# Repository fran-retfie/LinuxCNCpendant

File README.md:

# LinuxCNC Pendant

This is a pendant for linuxCNC using an SparkFun SAMD21 Dev Breakout but with little or no changes to the program you can run this on other arduino UNO style board.

## Getting Started

**warning** this project may require some changes to make it work properly with your hardware

The project is divided in 4 directories:
* model - a FreeCAD project of the enclosure and a G-code for cutting it
* PCB - a kicad project of the PCB
* Arduino
* Python

### Prerequisites

I suggest you check the PCB before starting beacause there will be maybe some issues: (eg: spacings, SMD parts filipped, ecc..)

for running python program you need the following packages:
* linuxCNC
* TkInter
* tk-tools
* pyserial

### Installing

Upload arduino 'remoteCNC' project on the board and run the python 'remoteCNC' program on a PC with linuxCNC running

## Running the tests

To check pushbuttons and analog input use the 'remoteCNC_test' program on both arduino and PC side.

## Contributing

This project expecially the software in not completed so you are free to contribuite in any way you want.

## Authors

* **Francesco Osti** - *Initial work* - [fran-retfie](https://github.com/fran-retfie)

See also the list of [contributors](https://github.com/fran-retfie/LinuxCNCpendant/contributors)

## License

This project is licensed under the MIT License - see the [LICENSE.md](LICENSE.md) file for details

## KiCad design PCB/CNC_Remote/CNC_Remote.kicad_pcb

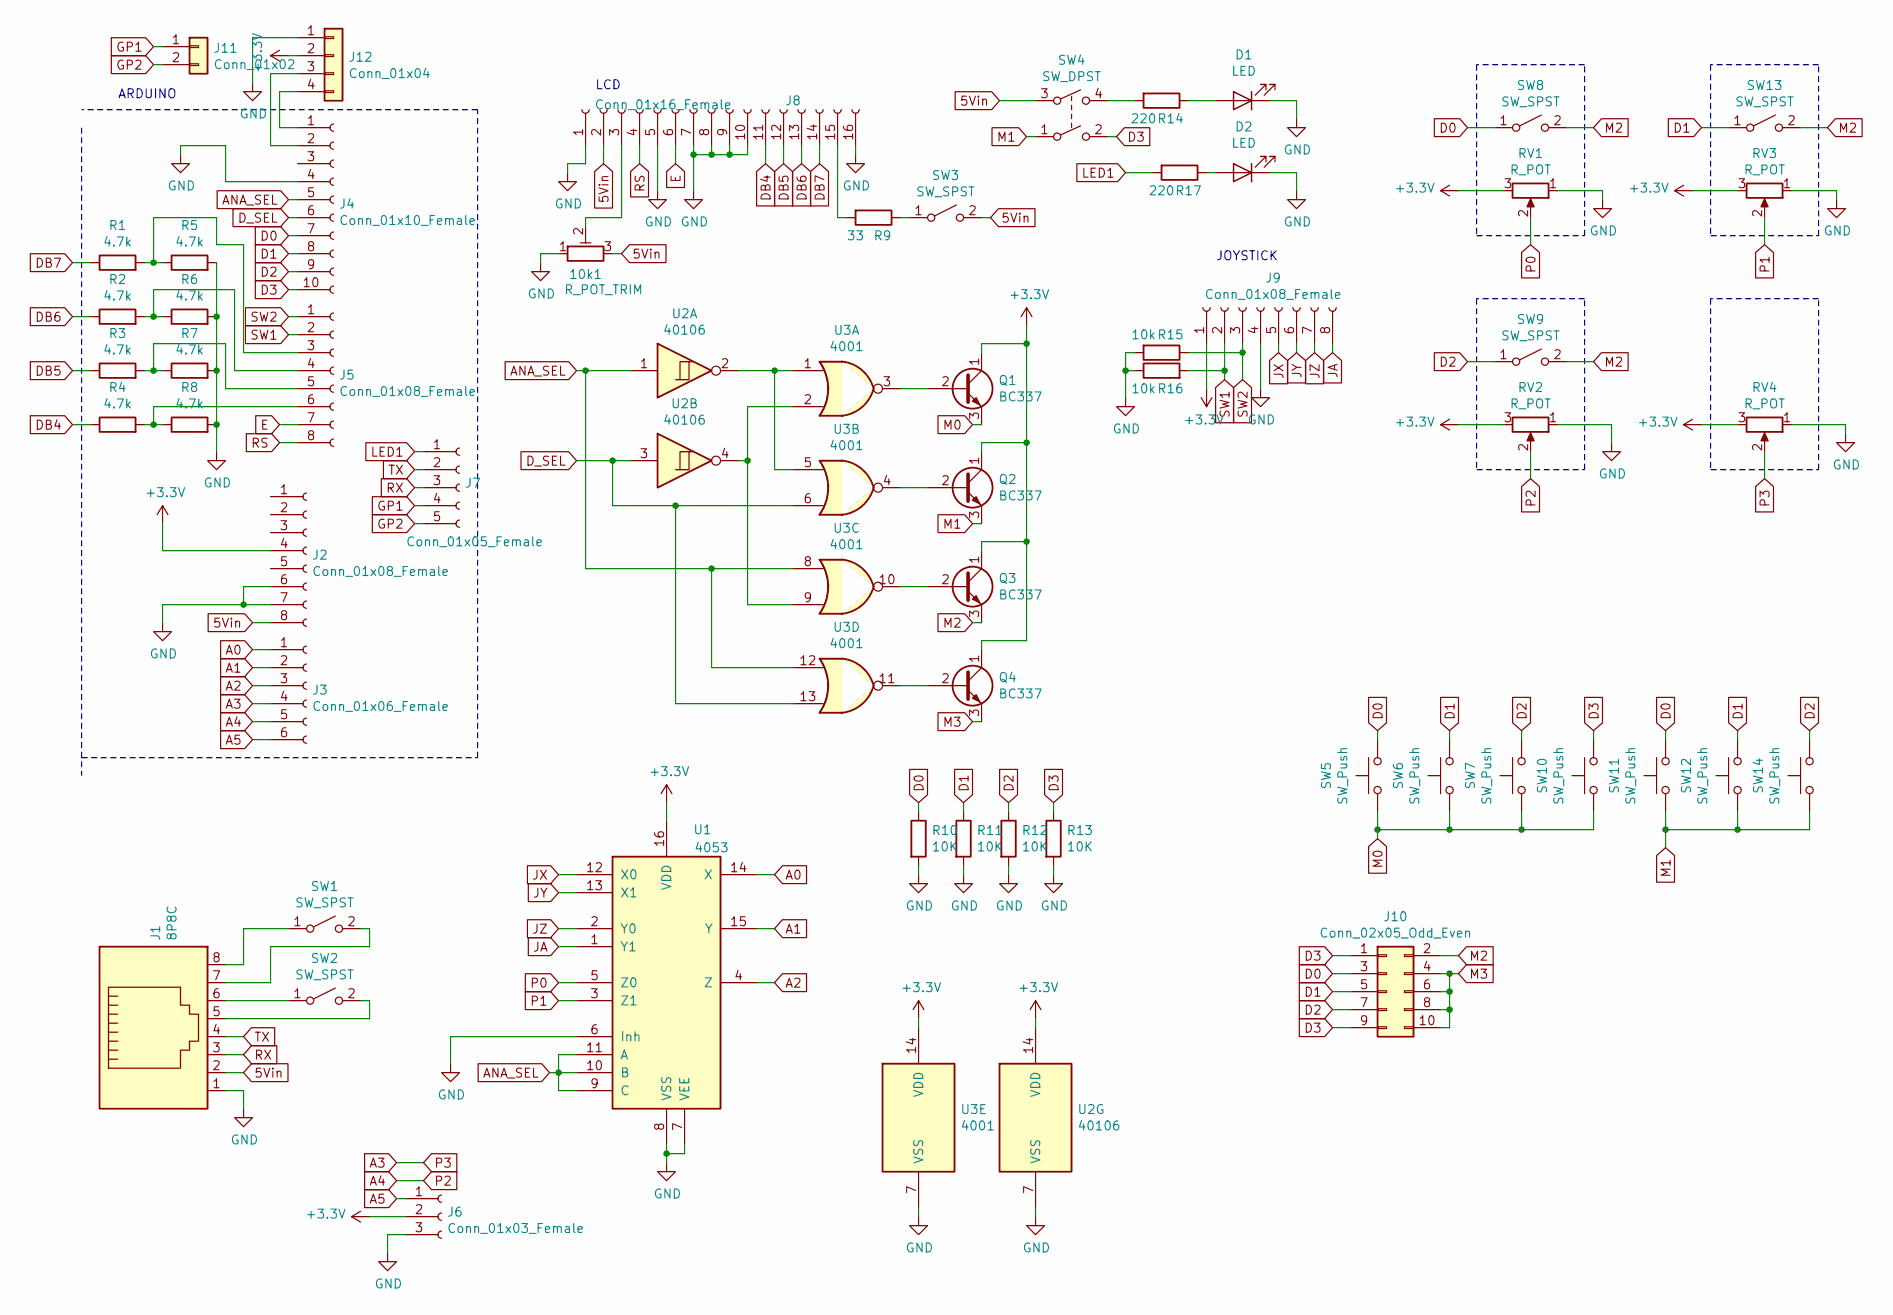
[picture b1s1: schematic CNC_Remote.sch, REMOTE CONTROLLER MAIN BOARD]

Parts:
10k1: R_POT_TRIM; Potentiometer_Piher_PT-10-V10_Vertical
D1, D2: LED; PinHeader_1x02_P2.54mm_Vertical
J1: 8P8C; RJ45_Amphenol_54602-x08_Horizontal
J2, J5, J9: Conn_01x08_Female; PinHeader_1x08_P2.54mm_Vertical
J3: Conn_01x06_Female; PinHeader_1x06_P2.54mm_Vertical
J4: Conn_01x10_Female; PinHeader_1x10_P2.54mm_Vertical
J6: Conn_01x03_Female; PinHeader_1x03_P2.54mm_Vertical
J7: Conn_01x05_Female; PinHeader_1x05_P2.54mm_Vertical
J8: Conn_01x16_Female; PinHeader_1x16_P2.54mm_Vertical
J10: Conn_02x05_Odd_Even; PinHeader_2x05_P2.54mm_Horizontal
J11: Conn_01x02; PinHeader_1x02_P2.54mm_Vertical
J12: Conn_01x04; PinHeader_1x04_P2.54mm_Vertical
Q1, Q2, Q3, Q4: BC337; TO-92_Inline
R1, R2, R3, R4, R5, R6, R7, R8: 4.7k; R_Axial_DIN0207_L6.3mm_D2.5mm_P10.16mm_Horizontal
R9: 33; R_Axial_DIN0207_L6.3mm_D2.5mm_P10.16mm_Horizontal
R10, R11, R12, R13: 10K; R_Axial_DIN0207_L6.3mm_D2.5mm_P10.16mm_Horizontal
R14, R17: 220; R_Axial_DIN0207_L6.3mm_D2.5mm_P10.16mm_Horizontal
R15, R16: 10k; R_Axial_DIN0207_L6.3mm_D2.5mm_P10.16mm_Horizontal
RV1, RV2, RV3, RV4: R_POT; PinHeader_1x03_P2.54mm_Vertical
SW1, SW2, SW3, SW8, SW9, SW13: SW_SPST; PinHeader_1x02_P2.54mm_Vertical
SW4: SW_DPST; PinHeader_1x04_P2.54mm_Vertical
SW5, SW6, SW7, SW10, SW11, SW12, SW14: SW_Push; PinHeader_1x02_P2.54mm_Vertical
U1: 4053; SOIC-16W_5.3x10.2mm_P1.27mm
U2: 40106; DIP-14_W7.62mm_Socket_LongPads
U3: 4001; DIP-14_W7.62mm_Socket_LongPads

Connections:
5Vin: 10k1.3, J1.2, J2.8, J8.2, SW3.2 (B), SW4.3
+3V3: J2.4, J6.2, J9.1, J12.2, Q1.1 (C), Q2.1 (C), Q3.1 (C), Q4.1 (C), RV1.3, RV2.3, RV3.3, RV4.3, U1.16 (VDD), U2.14 (VDD), U3.14 (VDD)
A0: J3.1, U1.14 (X)
A1: J3.2, U1.15 (Y)
A2: J3.3, U1.4 (Z)
A3: J3.4, RV4.2
A4: J3.5, RV2.2
A5: J3.6, J6.1
ANA_SEL: J4.5, U1.9 (C), U1.10 (B), U1.11 (A), U2.1, U3.8, U3.12
D0: J4.7, J10.3, R10.1, SW5.2, SW8.1 (A), SW11.2
D1: J4.8, J10.5, R11.1, SW6.2, SW12.2, SW13.1 (A)
D2: J4.9, J10.7, R12.1, SW7.2, SW9.1 (A), SW14.2
D3: J4.10, J10.1, J10.9, R13.1, SW4.2, SW10.2
DB4: J8.11, R4.1
DB5: J8.12, R3.1
DB6: J8.13, R2.1
DB7: J8.14, R1.1
D_SEL: J4.6, U2.3, U3.6, U3.13
E: J5.7, J8.6
GND: 10k1.1, D1.1 (K), D2.1 (K), J1.1, J2.6, J2.7, J4.4, J6.3, J8.1, J8.5, J8.7, J8.8, J8.9, J8.10, J8.16, J9.4, J12.1, R5.2, R6.2, R7.2, R8.2, R10.2, R11.2, R12.2, R13.2, R15.2, R16.1, RV1.1, RV2.1, RV3.1, RV4.1, U1.6 (Inh), U1.7 (VEE), U1.8 (VSS), U2.7 (VSS), U3.7 (VSS)
GP1: J7.4, J11.1
GP2: J7.5, J11.2
JA: J9.8, U1.1 (Y1)
JX: J9.5, U1.12 (X0)
JY: J9.6, U1.13 (X1)
JZ: J9.7, U1.2 (Y0)
LED1: J7.1, R17.2
M0: Q1.3 (E), SW5.1, SW6.1, SW7.1, SW10.1
M1: Q2.3 (E), SW4.1, SW11.1, SW12.1, SW14.1
M2: J10.2, Q3.3 (E), SW8.2 (B), SW9.2 (B), SW13.2 (B)
M3: J10.4, J10.6, J10.8, J10.10, Q4.3 (E)
unnamed: 10k1.2, J8.3
unnamed: D1.2 (A), R14.1
unnamed: D2.2 (A), R17.1
unnamed: J1.5, SW2.2 (B)
unnamed: J1.6, SW2.1 (A)
unnamed: J1.7, SW1.2 (B)
unnamed: J1.8, SW1.1 (A)
unnamed: J5.3, R1.2, R5.1
unnamed: J5.4, R2.2, R6.1
unnamed: J5.5, R3.2, R7.1
unnamed: J5.6, R4.2, R8.1
unnamed: J8.15, R9.2
unnamed: J4.2, J12.3
unnamed: J4.1, J12.4
unnamed: Q1.2 (B), U3.3
unnamed: Q2.2 (B), U3.4
unnamed: Q3.2 (B), U3.10
unnamed: Q4.2 (B), U3.11
unnamed: R9.1, SW3.1 (A)
unnamed: R14.2, SW4.4
unnamed: U2.2, U3.1, U3.5
unnamed: U2.4, U3.2, U3.9
P0: RV1.2, U1.5 (Z0)
P1: RV3.2, U1.3 (Z1)
RS: J5.8, J8.4
RX: J1.3, J7.3
SW1: J5.2, J9.2, R16.2
SW2: J5.1, J9.3, R15.1
TX: J1.4, J7.2

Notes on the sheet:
ARDUINO
LCD
JOYSTICK

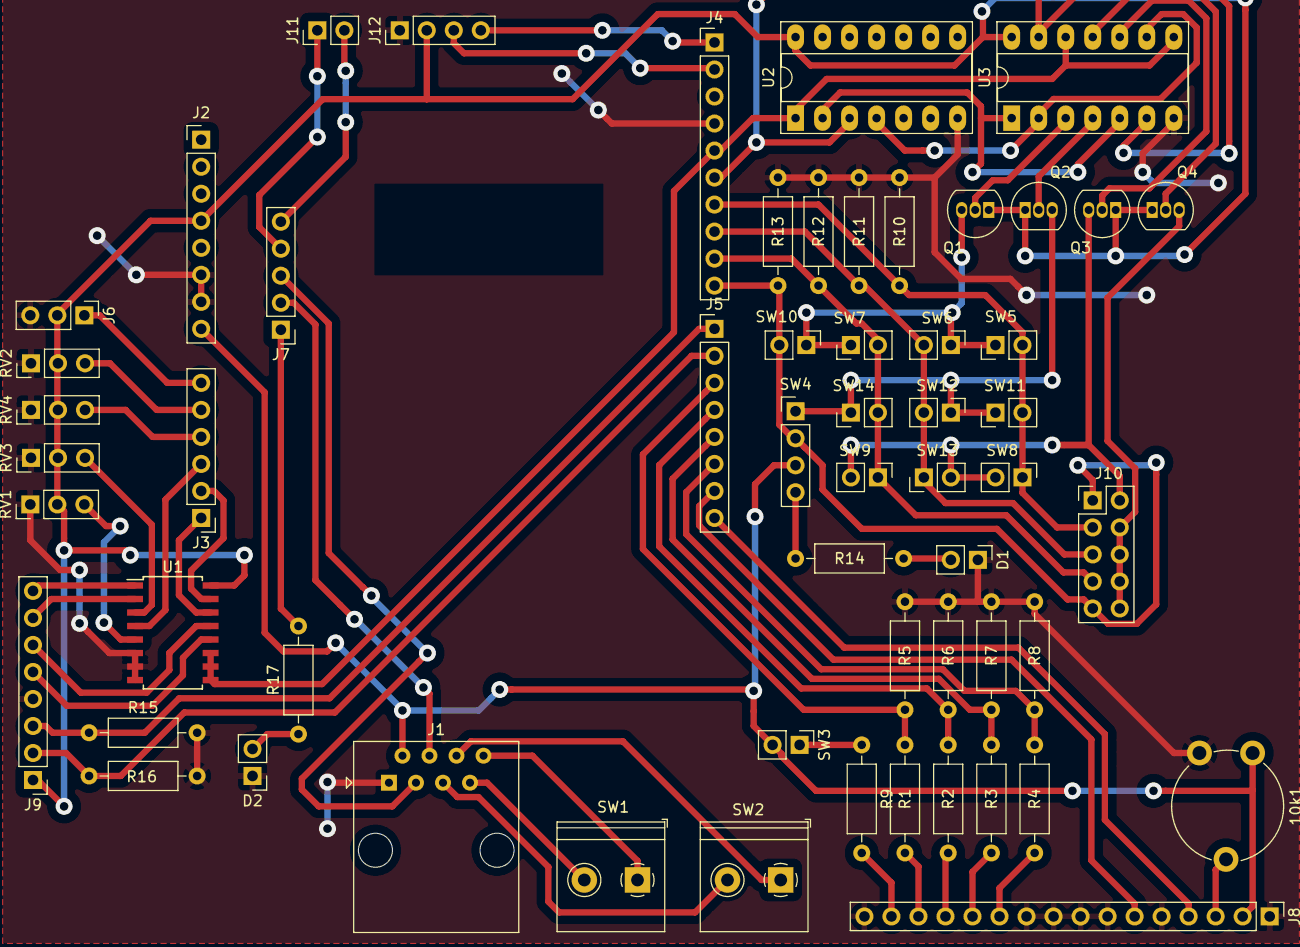
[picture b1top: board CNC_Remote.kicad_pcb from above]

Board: 2 copper layers, 57 parts (0 on the bottom side), 60 nets.

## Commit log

2019-09-01 second commit
